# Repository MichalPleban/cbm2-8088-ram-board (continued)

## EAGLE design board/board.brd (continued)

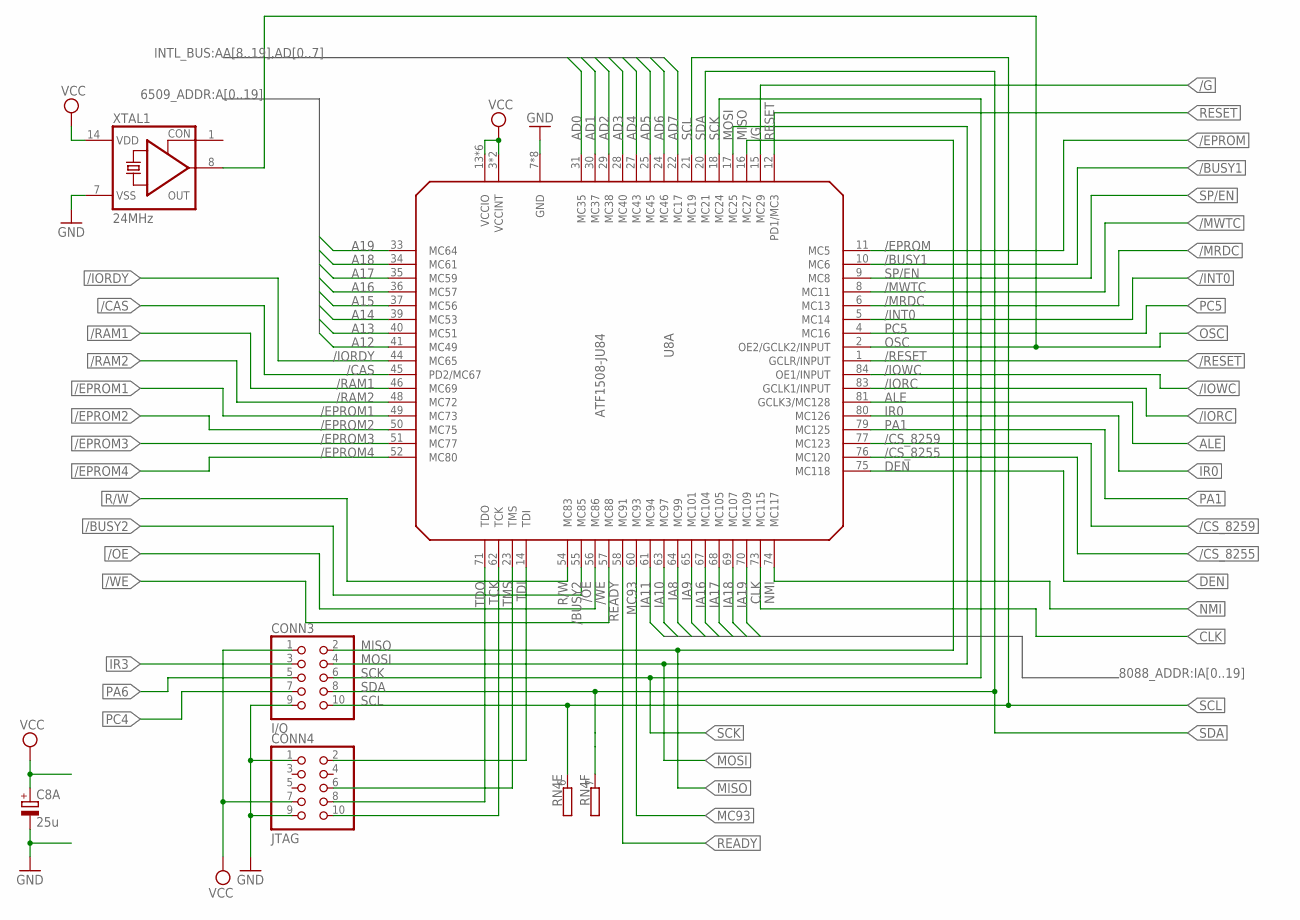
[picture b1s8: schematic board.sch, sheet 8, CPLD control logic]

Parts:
C8A: 25u; E5-6
CONN3: I/O; 2X05
CONN4: JTAG; 2X05
RN4: GE08R; SIL9
U8A: ATF1508-JU84; S84
XTAL1: 24MHz; SG51

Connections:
/BUSY1: U8A.10 (MC6); also elsewhere on the board
/BUSY2: U8A.55 (MC85); also elsewhere on the board
/CAS: U8A.45 (PD2/MC67); also elsewhere on the board
/CS_8255: U8A.76 (MC120); also elsewhere on the board
/CS_8259: U8A.77 (MC123); also elsewhere on the board
/EPROM: U8A.11 (MC5); also elsewhere on the board
/EPROM1: U8A.49 (MC73); also elsewhere on the board
/EPROM2: U8A.50 (MC75); also elsewhere on the board
/EPROM3: U8A.51 (MC77); also elsewhere on the board
/EPROM4: U8A.52 (MC80); also elsewhere on the board
/G: U8A.15 (MC29); also elsewhere on the board
/INT0: U8A.5 (MC14); also elsewhere on the board
/IORC: U8A.83 (GCLK1/INPUT); also elsewhere on the board
/IORDY: U8A.44 (MC65); also elsewhere on the board
/IOWC: U8A.84 (OE1/INPUT); also elsewhere on the board
/MRDC: U8A.6 (MC13); also elsewhere on the board
/MWTC: U8A.8 (MC11); also elsewhere on the board
/OE: U8A.56 (MC86); also elsewhere on the board
/RAM1: U8A.46 (MC69); also elsewhere on the board
/RAM2: U8A.48 (MC72); also elsewhere on the board
/RESET: U8A.1 (GCLR/INPUT); also elsewhere on the board
/WE: U8A.57 (MC88); also elsewhere on the board
A12: U8A.41 (MC49); also elsewhere on the board
A13: U8A.40 (MC51); also elsewhere on the board
A14: U8A.39 (MC53); also elsewhere on the board
A15: U8A.37 (MC56); also elsewhere on the board
A16: U8A.36 (MC57); also elsewhere on the board
A17: U8A.35 (MC59); also elsewhere on the board
A18: U8A.34 (MC61); also elsewhere on the board
A19: U8A.33 (MC64); also elsewhere on the board
AD0: U8A.31 (MC35); also elsewhere on the board
AD1: U8A.30 (MC37); also elsewhere on the board
AD2: U8A.29 (MC38); also elsewhere on the board
AD3: U8A.28 (MC40); also elsewhere on the board
AD4: U8A.27 (MC43); also elsewhere on the board
AD5: U8A.25 (MC45); also elsewhere on the board
AD6: U8A.24 (MC46); also elsewhere on the board
AD7: U8A.22 (MC17); also elsewhere on the board
ALE: U8A.81 (GCLK3/MC128); also elsewhere on the board
CLK: U8A.73 (MC115); also elsewhere on the board
DEN: U8A.75 (MC118); also elsewhere on the board
GND: C8A.-, CONN3.9, CONN4.1, CONN4.9, U8A.7 (GND), U8A.19 (GND), U8A.32 (GND), U8A.42 (GND), U8A.47 (GND), U8A.59 (GND), U8A.72 (GND), U8A.82 (GND), XTAL1.7 (VSS); also elsewhere on the board
IA8: U8A.64 (MC99); also elsewhere on the board
IA9: U8A.65 (MC101); also elsewhere on the board
IA10: U8A.63 (MC97); also elsewhere on the board
IA11: U8A.61 (MC94); also elsewhere on the board
IA16: U8A.67 (MC104); also elsewhere on the board
IA17: U8A.68 (MC105); also elsewhere on the board
IA18: U8A.69 (MC107); also elsewhere on the board
IA19: U8A.70 (MC109); also elsewhere on the board
IR0: U8A.80 (MC126); also elsewhere on the board
IR3: CONN3.3; also elsewhere on the board
MC93: U8A.60 (MC93); also elsewhere on the board
MISO: CONN3.2, U8A.16 (MC27); also elsewhere on the board
MOSI: CONN3.4, U8A.17 (MC25); also elsewhere on the board
NMI: U8A.74 (MC117); also elsewhere on the board
OSC: U8A.2 (OE2/GCLK2/INPUT), XTAL1.8 (OUT); also elsewhere on the board
PA1: U8A.79 (MC125); also elsewhere on the board
PA6: CONN3.5; also elsewhere on the board
PC4: CONN3.7; also elsewhere on the board
PC5: U8A.4 (MC16); also elsewhere on the board
R/W: U8A.54 (MC83); also elsewhere on the board
READY: U8A.58 (MC91); also elsewhere on the board
RESET: U8A.12 (PD1/MC3); also elsewhere on the board
SCK: CONN3.6, U8A.18 (MC24); also elsewhere on the board
SCL: CONN3.10, RN4.6 (2), U8A.21 (MC19); also elsewhere on the board
SDA: CONN3.8, RN4.7 (2), U8A.20 (MC21); also elsewhere on the board
SP/EN: U8A.9 (MC8); also elsewhere on the board
TCK: CONN4.10, U8A.62 (TCK)
TDI: CONN4.2, U8A.14 (TDI)
TDO: CONN4.8, U8A.71 (TDO)
TMS: CONN4.6, U8A.23 (TMS)
VCC: C8A.+, CONN3.1, CONN4.7, U8A.3 (VCCINT), U8A.13 (VCCIO), U8A.26 (VCCIO), U8A.38 (VCCIO), U8A.43 (VCCINT), U8A.53 (VCCIO), U8A.66 (VCCIO), U8A.78 (VCCIO), XTAL1.14 (VDD); also elsewhere on the board

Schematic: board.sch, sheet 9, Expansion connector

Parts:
CONN5: ISA; 2X30
RN4: GE08R; SIL9

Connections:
+12V: CONN5.15; also elsewhere on the board
-12V: CONN5.11; also elsewhere on the board
/AIOWC: CONN5.23; also elsewhere on the board
/AMWC: CONN5.19; also elsewhere on the board
/IORC: CONN5.25; also elsewhere on the board
/IORDY: CONN5.18, RN4.4 (2); also elsewhere on the board
/IOWC: CONN5.55; also elsewhere on the board
/MRDC: CONN5.21; also elsewhere on the board
/MWTC: CONN5.20; also elsewhere on the board
AD0: CONN5.16; also elsewhere on the board
AD1: CONN5.14; also elsewhere on the board
AD2: CONN5.12; also elsewhere on the board
AD3: CONN5.10; also elsewhere on the board
AD4: CONN5.8; also elsewhere on the board
AD5: CONN5.6; also elsewhere on the board
AD6: CONN5.4; also elsewhere on the board
AD7: CONN5.2; also elsewhere on the board
ALE: CONN5.53; also elsewhere on the board
CLK: CONN5.37; also elsewhere on the board
GND: CONN5.59; also elsewhere on the board
IA0: CONN5.60; also elsewhere on the board
IA1: CONN5.58; also elsewhere on the board
IA2: CONN5.56; also elsewhere on the board
IA3: CONN5.54; also elsewhere on the board
IA4: CONN5.52; also elsewhere on the board
IA5: CONN5.50; also elsewhere on the board
IA6: CONN5.48; also elsewhere on the board
IA7: CONN5.46; also elsewhere on the board
IA8: CONN5.44; also elsewhere on the board
IA9: CONN5.42; also elsewhere on the board
IA10: CONN5.40; also elsewhere on the board
IA11: CONN5.38; also elsewhere on the board
IA12: CONN5.36; also elsewhere on the board
IA13: CONN5.34; also elsewhere on the board
IA14: CONN5.32; also elsewhere on the board
IA15: CONN5.30; also elsewhere on the board
IA16: CONN5.28; also elsewhere on the board
IA17: CONN5.26; also elsewhere on the board
IA18: CONN5.24; also elsewhere on the board
IA19: CONN5.22; also elsewhere on the board
IR3: CONN5.47; also elsewhere on the board
IR4: CONN5.45; also elsewhere on the board
IR5: CONN5.41; also elsewhere on the board
IR6: CONN5.39; also elsewhere on the board
MC93: CONN5.27; also elsewhere on the board
MISO: CONN5.31; also elsewhere on the board
MOSI: CONN5.33, RN4.9 (2); also elsewhere on the board
OSC: CONN5.57; also elsewhere on the board
PA2: CONN5.5, RN4.5 (2); also elsewhere on the board
PA6: CONN5.13; also elsewhere on the board
PA7: CONN5.17, RN4.2; also elsewhere on the board
PC3: CONN5.43; also elsewhere on the board
PC4: CONN5.9; also elsewhere on the board
PC7: CONN5.7; also elsewhere on the board
RESET: CONN5.1; also elsewhere on the board
SCK: CONN5.29, RN4.8 (2); also elsewhere on the board
SCL: CONN5.51; also elsewhere on the board
SDA: CONN5.49; also elsewhere on the board
SQW: CONN5.35; also elsewhere on the board
VCC: CONN5.3, RN4.1; also elsewhere on the board

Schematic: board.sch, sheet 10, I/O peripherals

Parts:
C10A, C10B, C10C, C10D: 100n; C050-025X075
C10E: 25u; E5-6
G1: CR2032V
IC1: LP2950Z; TO92
J1: SDCARD; SDCMF-10915W010
JP1: JP1E; JP1
LED1, LED2: LEDSQR5.7X3.2; U57X32
R1, R2: 4.7k; 0207/10
RN4: GE08R; SIL9
U10A: 4050N; DIL16
U10B: DS1307; DIL08
U10C: 24C64P; DIL8
XTAL2: CRYSTALTC38H; TC38H

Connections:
+3V3: C10A.1, C10E.+, IC1.1 (O), J1.4 (VDD), LED1.A, R2.2, U10A.1 (VDD)
/BUSY2: U10A.9 (I); also elsewhere on the board
BATT: G1.+, U10B.3 (VBAT)
CS': J1.1 (CD/DAT3/CS), U10A.6 (O)
GND: C10A.2, C10B.2, C10C.2, C10D.2, C10E.-, G1.-, IC1.2 (GND), J1.3 (VSS1), J1.6 (VSS2), J1.M1 (GND), J1.M2 (GND), J1.M3 (GND), J1.M4 (GND), LED2.K (C), R1.1, U10A.8 (VSS), U10B.4 (GND), U10C.2 (A1), U10C.3 (A2), U10C.4 (GND), U10C.7 (WP); also elsewhere on the board
LED1: LED1.K (C), U10A.10 (O)
LED2: LED2.A, U10A.12 (O)
MISO: J1.7 (DAT0/DO), R2.1; also elsewhere on the board
MOSI: U10A.3 (I); also elsewhere on the board
MOSI': J1.2 (CMD/DI), U10A.2 (O)
unnamed: JP1.2, R1.2, U10C.1 (A0)
PC0: U10A.11 (I); also elsewhere on the board
PC7: U10A.7 (I); also elsewhere on the board
SCK: U10A.5 (I); also elsewhere on the board
SCK': J1.5 (CLK/SCLK), U10A.4 (O)
SCL: C10D.1, U10B.6 (SCL), U10C.6 (SCL); also elsewhere on the board
SDA: U10B.5 (SDA), U10C.5 (SDA); also elsewhere on the board
SQW: RN4.3 (2), U10B.7 (SQW); also elsewhere on the board
VCC: C10B.1, C10C.1, IC1.3 (I), JP1.1, U10B.8 (VCC), U10C.8 (VCC); also elsewhere on the board
XTAL1: U10B.1 (X1), XTAL2.2
XTAL2: U10B.2 (X2), XTAL2.1

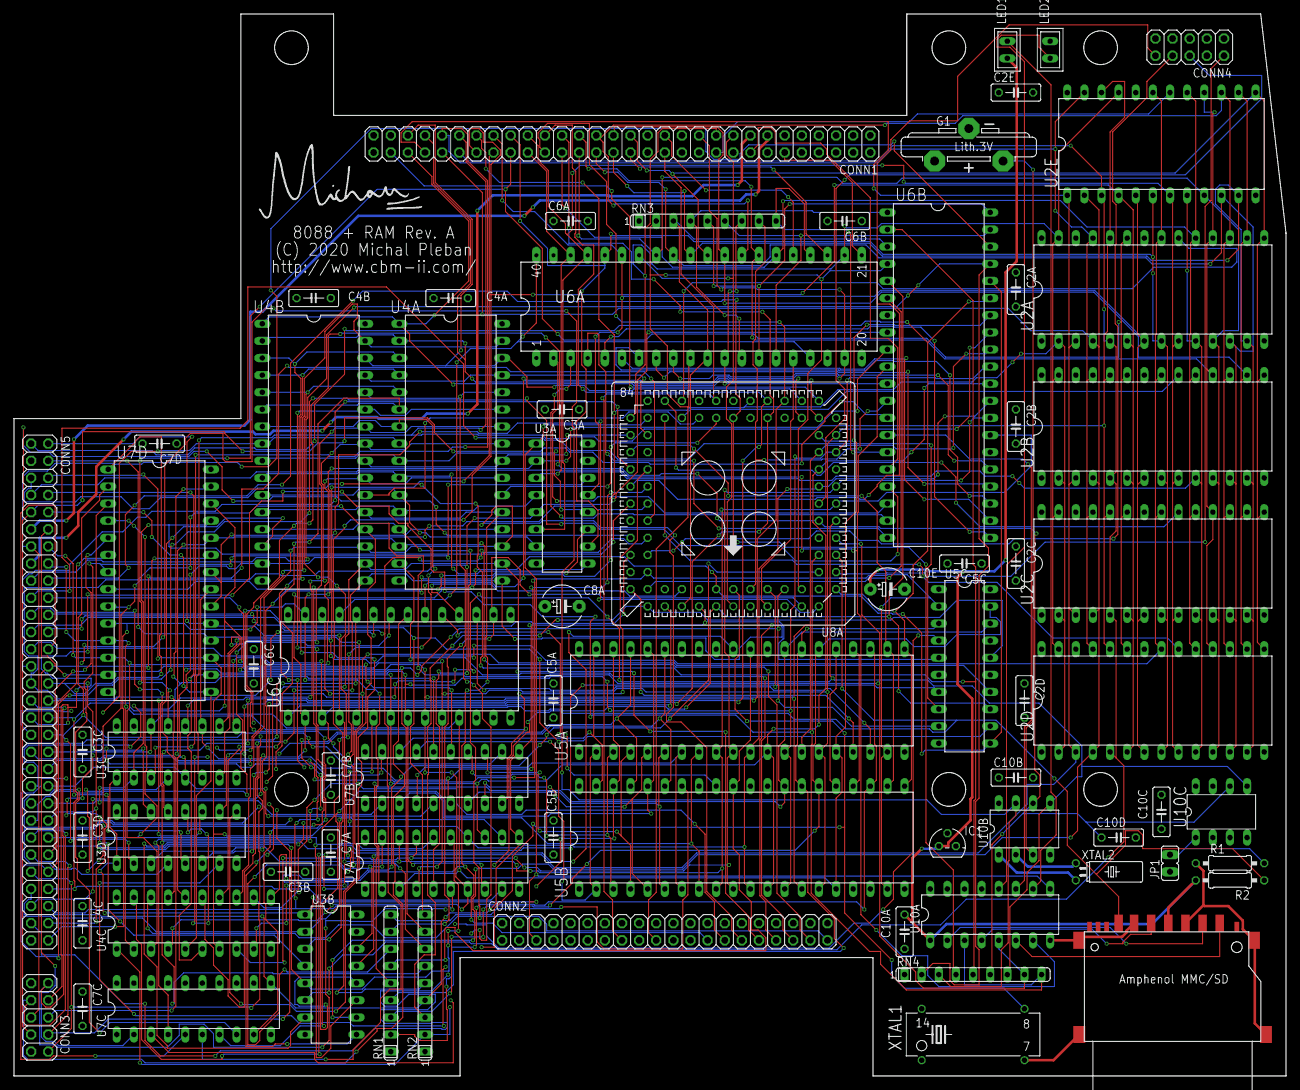
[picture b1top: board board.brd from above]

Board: 4 copper layers, 188.7 x 157.5 mm, 73 parts (0 on the bottom side), 197 nets.

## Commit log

2021-02-06 Revision A
